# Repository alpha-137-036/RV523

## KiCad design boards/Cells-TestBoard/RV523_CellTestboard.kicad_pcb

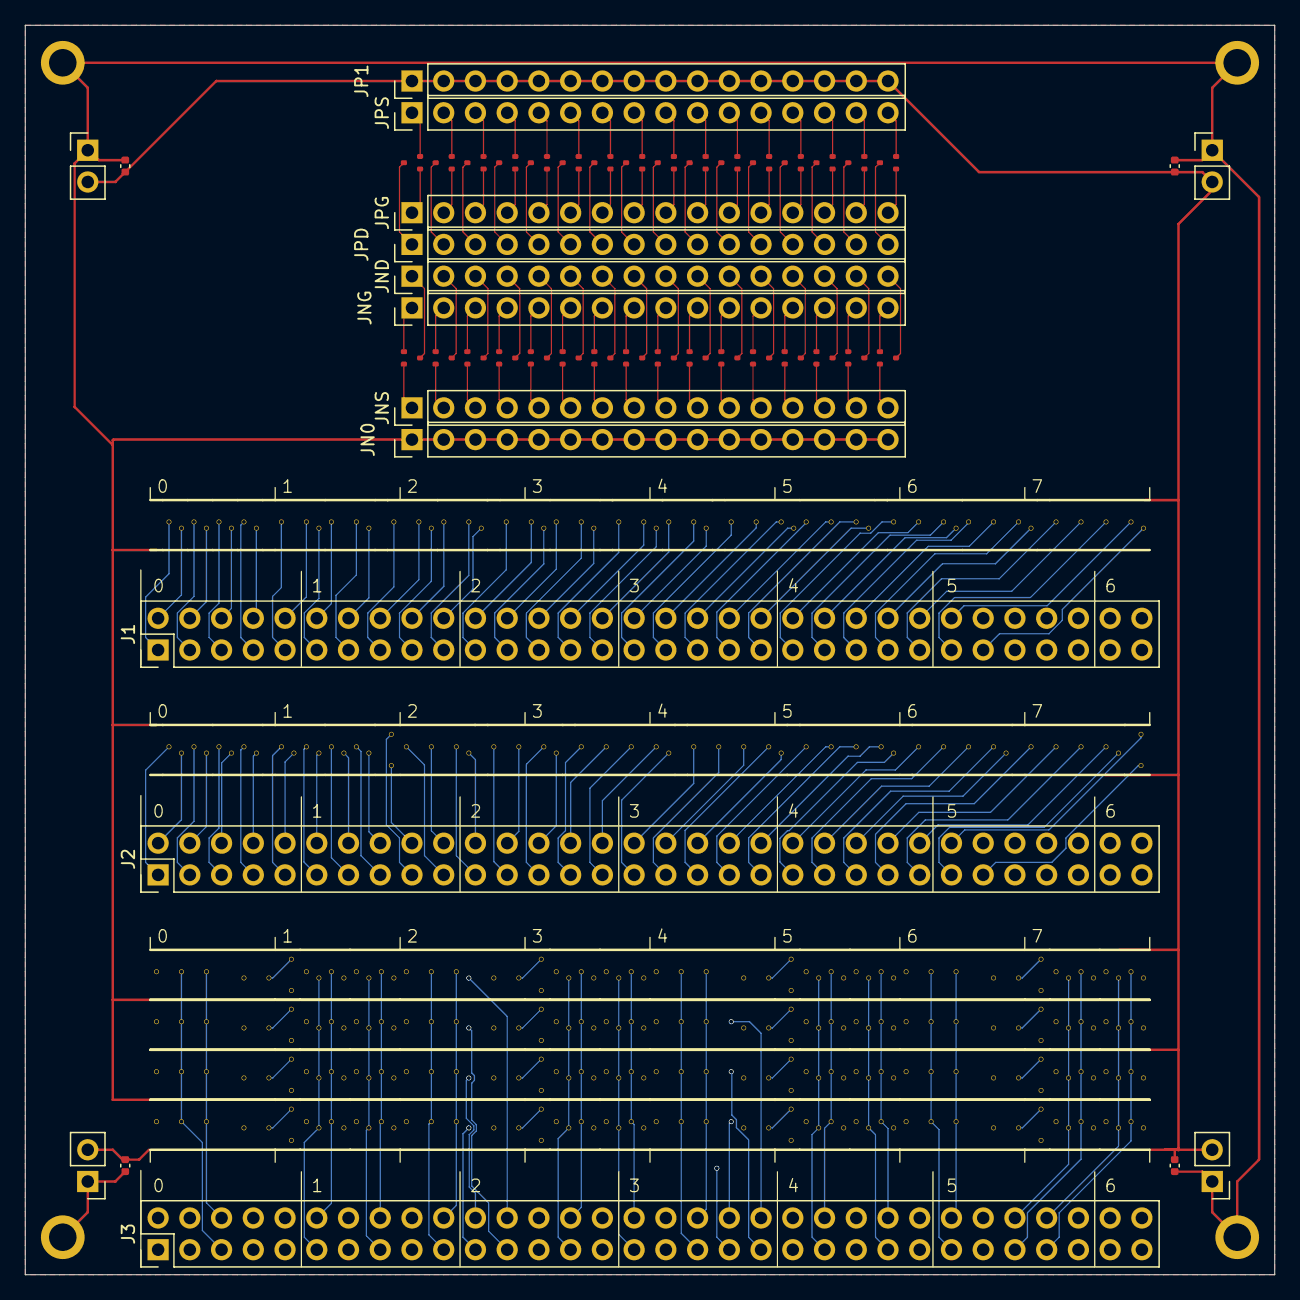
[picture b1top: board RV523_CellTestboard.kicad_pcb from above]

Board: 4 copper layers, 100.0 x 100.0 mm, 161 parts (0 on the bottom side), 276 nets.

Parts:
AOI21_1: AOI21
AOI22_1: AOI22
AOI211_1: AOI211
DECAP1, DECAP2, DECAP3, DECAP4: C_0402_1005Metric
DECAP_1, DECAP_2, DECAP_3, DECAP_4, DECAP_5, DECAP_6, DECAP_7, DECAP_8, DECAP_10, DECAP_11, DECAP_13, DECAP_14, DECAP_15, DECAP_16, DECAP_17, DECAP_18: DECAP
DECAP_LED_12, DECAP_LED_19: DECAP_LED
J1, J2, J3: PinHeader_2x32_P2.54mm_Vertical
JN0: PinHeader_1x16_P2.54mm_Vertical
JND: PinHeader_1x16_P2.54mm_Vertical
JNG: PinHeader_1x16_P2.54mm_Vertical
JNS: PinHeader_1x16_P2.54mm_Vertical
JP1: PinHeader_1x16_P2.54mm_Vertical
JPD: PinHeader_1x16_P2.54mm_Vertical
JPG: PinHeader_1x16_P2.54mm_Vertical
JPS: PinHeader_1x16_P2.54mm_Vertical
JSupply1, JSupply2, JSupply3, JSupply4: PinHeader_1x02_P2.54mm_Vertical
NAND2_1, NAND2_2, NAND2_3, NAND2_4: NAND2
NAND3_1, NAND3_2: NAND3
NAND4_1: NAND4
NOR2_1, NOR2_2, NOR2_3, NOR2_4: NOR2
NOR3_1, NOR3_2: NOR3
NOR4_1: NOR4
NOT_1, NOT_2, NOT_3, NOT_4: NOT
OAI21_1: OAI21
OAI22_1: OAI22
OAI211_1: OAI211
TINV_1, TINV_2, TINV_3, TINV_4: TINV
genblk1[1].N, genblk1[2].N, genblk1[3].N, genblk1[4].N, genblk1[5].N, genblk1[6].N, genblk1[7].N, genblk1[8].N, genblk1[9].N, genblk1[10].N, genblk1[11].N, genblk1[12].N, genblk1[13].N, genblk1[14].N, genblk1[15].N, genblk1[16].N: NMOS; SOT523
genblk1[1].P, genblk1[2].P, genblk1[3].P, genblk1[4].P, genblk1[5].P, genblk1[6].P, genblk1[7].P, genblk1[8].P, genblk1[9].P, genblk1[10].P, genblk1[11].P, genblk1[12].P, genblk1[13].P, genblk1[14].P, genblk1[15].P, genblk1[16].P: PMOS; SOT523
genblk2[0].genblk1[0].D, genblk2[0].genblk1[1].D, genblk2[0].genblk1[2].D, genblk2[0].genblk1[3].D, genblk2[1].genblk1[0].D, genblk2[1].genblk1[1].D, genblk2[1].genblk1[2].D, genblk2[1].genblk1[3].D, genblk2[2].genblk1[0].D, genblk2[2].genblk1[1].D, genblk2[2].genblk1[2].D, genblk2[2].genblk1[3].D, genblk2[3].genblk1[0].D, genblk2[3].genblk1[1].D, genblk2[3].genblk1[2].D, genblk2[3].genblk1[3].D: DECAP_LED
genblk2[0].genblk1[0].L, genblk2[0].genblk1[1].L, genblk2[0].genblk1[2].L, genblk2[0].genblk1[3].L, genblk2[1].genblk1[0].L, genblk2[1].genblk1[1].L, genblk2[1].genblk1[2].L, genblk2[1].genblk1[3].L, genblk2[2].genblk1[0].L, genblk2[2].genblk1[1].L, genblk2[2].genblk1[2].L, genblk2[2].genblk1[3].L, genblk2[3].genblk1[0].L, genblk2[3].genblk1[1].L, genblk2[3].genblk1[2].L, genblk2[3].genblk1[3].L: D_LATCH
genblk2[0].genblk1[0].R1, genblk2[0].genblk1[0].R2, genblk2[0].genblk1[1].R1, genblk2[0].genblk1[1].R2, genblk2[0].genblk1[2].R1, genblk2[0].genblk1[2].R2, genblk2[0].genblk1[3].R1, genblk2[0].genblk1[3].R2, genblk2[1].genblk1[0].R1, genblk2[1].genblk1[0].R2, genblk2[1].genblk1[1].R1, genblk2[1].genblk1[1].R2, genblk2[1].genblk1[2].R1, genblk2[1].genblk1[2].R2, genblk2[1].genblk1[3].R1, genblk2[1].genblk1[3].R2, genblk2[2].genblk1[0].R1, genblk2[2].genblk1[0].R2, genblk2[2].genblk1[1].R1, genblk2[2].genblk1[1].R2, genblk2[2].genblk1[2].R1, genblk2[2].genblk1[2].R2, genblk2[2].genblk1[3].R1, genblk2[2].genblk1[3].R2, genblk2[3].genblk1[0].R1, genblk2[3].genblk1[0].R2, genblk2[3].genblk1[1].R1, genblk2[3].genblk1[1].R2, genblk2[3].genblk1[2].R1, genblk2[3].genblk1[2].R2, genblk2[3].genblk1[3].R1, genblk2[3].genblk1[3].R2: TINV

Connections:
GND: DECAP1.2, DECAP2.2, DECAP3.2, DECAP4.2, JN0.1 (pins.1), JN0.2 (pins.2), JN0.3 (pins.3), JN0.4 (pins.4), JN0.5 (pins.5), JN0.6 (pins.6), JN0.7 (pins.7), JN0.8 (pins.8), JN0.9 (pins.9), JN0.10 (pins.10), JN0.11 (pins.11), JN0.12 (pins.12), JN0.13 (pins.13), JN0.14 (pins.14), JN0.15 (pins.15), JN0.16 (pins.16), JSupply1.1 (pins.1), JSupply2.1 (pins.1), JSupply3.1 (pins.1), JSupply4.1 (pins.1)
J1pins.9: J1.9 (pins.9), NAND2_1.A1
J1pins.10: J1.10 (pins.10), NAND2_1.A2
J1pins.12: J1.12 (pins.12), NAND2_2.A1
J1pins.13: J1.13 (pins.13), NAND2_2.A2
J1pins.15: J1.15 (pins.15), NAND2_3.A1
J1pins.16: J1.16 (pins.16), NAND2_3.A2
J1pins.18: J1.18 (pins.18), NAND2_4.A1
J1pins.19: J1.19 (pins.19), NAND2_4.A2
J1pins.21: J1.21 (pins.21), NOR2_1.A1
J1pins.22: J1.22 (pins.22), NOR2_1.A2
J1pins.24: J1.24 (pins.24), NOR2_2.A1
J1pins.25: J1.25 (pins.25), NOR2_2.A2
J1pins.27: J1.27 (pins.27), NOR2_3.A1
J1pins.28: J1.28 (pins.28), NOR2_3.A2
J1pins.30: J1.30 (pins.30), NOR2_4.A1
J1pins.31: J1.31 (pins.31), NOR2_4.A2
J1pins.33: J1.33 (pins.33), NAND3_1.A1
J1pins.34: J1.34 (pins.34), NAND3_1.A2
J1pins.35: J1.35 (pins.35), NAND3_1.A3
J1pins.37: J1.37 (pins.37), NAND3_2.A1
J1pins.38: J1.38 (pins.38), NAND3_2.A2
J1pins.39: J1.39 (pins.39), NAND3_2.A3
J1pins.41: J1.41 (pins.41), NOR3_1.A1
J1pins.42: J1.42 (pins.42), NOR3_1.A2
J1pins.43: J1.43 (pins.43), NOR3_1.A3
J1pins.45: J1.45 (pins.45), NOR3_2.A1
J1pins.46: J1.46 (pins.46), NOR3_2.A2
J1pins.47: J1.47 (pins.47), NOR3_2.A3
J1pins.49: J1.49 (pins.49), NAND4_1.A1
J1pins.50: J1.50 (pins.50), NAND4_1.A2
J1pins.51: J1.51 (pins.51), NAND4_1.A3
J1pins.52: J1.52 (pins.52), NAND4_1.A4
J1pins[1]: J1.1 (pins.1), NOT_1.A
J1pins[2]: J1.2 (pins.2), NOT_1.Y
J1pins[3]: J1.3 (pins.3), NOT_2.A
J1pins[4]: J1.4 (pins.4), NOT_2.Y
J1pins[5]: J1.5 (pins.5), NOT_3.A
J1pins[6]: J1.6 (pins.6), NOT_3.Y
J1pins[7]: J1.7 (pins.7), NOT_4.A
J1pins[8]: J1.8 (pins.8), NOT_4.Y
J1pins[11]: J1.11 (pins.11), NAND2_1.Y
J1pins[14]: J1.14 (pins.14), NAND2_2.Y
J1pins[17]: J1.17 (pins.17), NAND2_3.Y
J1pins[20]: J1.20 (pins.20), NAND2_4.Y
J1pins[23]: J1.23 (pins.23), NOR2_1.Y
J1pins[26]: J1.26 (pins.26), NOR2_2.Y
J1pins[29]: J1.29 (pins.29), NOR2_3.Y
J1pins[32]: J1.32 (pins.32), NOR2_4.Y
J1pins[36]: J1.36 (pins.36), NAND3_1.Y
J1pins[40]: J1.40 (pins.40), NAND3_2.Y
J1pins[44]: J1.44 (pins.44), NOR3_1.Y
J1pins[48]: J1.48 (pins.48), NOR3_2.Y
J1pins[53]: J1.53 (pins.53), NAND4_1.Y
J2pins.1: J2.1 (pins.1), TINV_1.A
J2pins.2: J2.2 (pins.2), TINV_1.EN
J2pins.3: J2.3 (pins.3), TINV_1.nEN
J2pins.5: J2.5 (pins.5), TINV_2.A
J2pins.6: J2.6 (pins.6), TINV_2.EN
J2pins.7: J2.7 (pins.7), TINV_2.nEN
J2pins.9: J2.9 (pins.9), TINV_3.A
J2pins.10: J2.10 (pins.10), TINV_3.EN
J2pins.11: J2.11 (pins.11), TINV_3.nEN
J2pins.13: J2.13 (pins.13), TINV_4.A
J2pins.14: J2.14 (pins.14), TINV_4.EN
J2pins.15: J2.15 (pins.15), TINV_4.nEN
J2pins.19: AOI21_1.A, J2.19 (pins.19)
J2pins.20: AOI21_1.B1, J2.20 (pins.20)
J2pins.21: AOI21_1.B2, J2.21 (pins.21)
J2pins.23: J2.23 (pins.23), OAI21_1.A
J2pins.24: J2.24 (pins.24), OAI21_1.B1
J2pins.25: J2.25 (pins.25), OAI21_1.B2
J2pins.27: AOI22_1.A1, J2.27 (pins.27)
J2pins.28: AOI22_1.A2, J2.28 (pins.28)
J2pins.29: AOI22_1.B1, J2.29 (pins.29)
J2pins.30: AOI22_1.B2, J2.30 (pins.30)
J2pins.32: J2.32 (pins.32), OAI22_1.A1
J2pins.33: J2.33 (pins.33), OAI22_1.A2
J2pins.34: J2.34 (pins.34), OAI22_1.B1
J2pins.35: J2.35 (pins.35), OAI22_1.B2
J2pins.37: AOI211_1.A, J2.37 (pins.37)
J2pins.38: AOI211_1.B, J2.38 (pins.38)
J2pins.39: AOI211_1.C1, J2.39 (pins.39)
J2pins.40: AOI211_1.C2, J2.40 (pins.40)
J2pins.42: J2.42 (pins.42), OAI211_1.A
J2pins.43: J2.43 (pins.43), OAI211_1.B
J2pins.44: J2.44 (pins.44), OAI211_1.C1
J2pins.45: J2.45 (pins.45), OAI211_1.C2
J2pins.47: J2.47 (pins.47), NOR4_1.A1
J2pins.48: J2.48 (pins.48), NOR4_1.A2
J2pins.49: J2.49 (pins.49), NOR4_1.A3
J2pins.50: J2.50 (pins.50), NOR4_1.A4
J2pins[4]: J2.4 (pins.4), TINV_1.Y
J2pins[8]: J2.8 (pins.8), TINV_2.Y
J2pins[12]: J2.12 (pins.12), TINV_3.Y
J2pins[16]: J2.16 (pins.16), TINV_4.Y
J2pins[17]: DECAP_LED_12.A, J2.17 (pins.17)
J2pins[18]: DECAP_LED_12.LED_GND, J2.18 (pins.18)
J2pins[22]: AOI21_1.Y, J2.22 (pins.22)
J2pins[26]: J2.26 (pins.26), OAI21_1.Y
J2pins[31]: AOI22_1.Y, J2.31 (pins.31)
J2pins[36]: J2.36 (pins.36), OAI22_1.Y
J2pins[41]: AOI211_1.Y, J2.41 (pins.41)
J2pins[46]: J2.46 (pins.46), OAI211_1.Y
J2pins[51]: J2.51 (pins.51), NOR4_1.Y
J2pins[52]: DECAP_LED_19.A, J2.52 (pins.52)
J2pins[53]: DECAP_LED_19.LED_GND, J2.53 (pins.53)
J3pins.1: J3.1 (pins.1), genblk2[0].genblk1[0].L.D, genblk2[1].genblk1[0].L.D, genblk2[2].genblk1[0].L.D, genblk2[3].genblk1[0].L.D
J3pins.2: J3.2 (pins.2), genblk2[0].genblk1[1].L.D, genblk2[1].genblk1[1].L.D, genblk2[2].genblk1[1].L.D, genblk2[3].genblk1[1].L.D
J3pins.3: J3.3 (pins.3), genblk2[0].genblk1[2].L.D, genblk2[1].genblk1[2].L.D, genblk2[2].genblk1[2].L.D, genblk2[3].genblk1[2].L.D
J3pins.4: J3.4 (pins.4), genblk2[0].genblk1[3].L.D, genblk2[1].genblk1[3].L.D, genblk2[2].genblk1[3].L.D, genblk2[3].genblk1[3].L.D
J3pins.5: J3.5 (pins.5), genblk2[0].genblk1[0].L.CLK, genblk2[0].genblk1[1].L.CLK, genblk2[0].genblk1[2].L.CLK, genblk2[0].genblk1[3].L.CLK
J3pins.6: J3.6 (pins.6), genblk2[0].genblk1[0].L.nCLK, genblk2[0].genblk1[1].L.nCLK, genblk2[0].genblk1[2].L.nCLK, genblk2[0].genblk1[3].L.nCLK
J3pins.11: J3.11 (pins.11), genblk2[0].genblk1[0].R1.EN, genblk2[0].genblk1[1].R1.EN, genblk2[0].genblk1[2].R1.EN, genblk2[0].genblk1[3].R1.EN
J3pins.12: J3.12 (pins.12), genblk2[0].genblk1[0].R1.nEN, genblk2[0].genblk1[1].R1.nEN, genblk2[0].genblk1[2].R1.nEN, genblk2[0].genblk1[3].R1.nEN
J3pins.15: J3.15 (pins.15), genblk2[0].genblk1[0].R2.EN, genblk2[0].genblk1[1].R2.EN, genblk2[0].genblk1[2].R2.EN, genblk2[0].genblk1[3].R2.EN
J3pins.16: J3.16 (pins.16), genblk2[0].genblk1[0].R2.nEN, genblk2[0].genblk1[1].R2.nEN, genblk2[0].genblk1[2].R2.nEN, genblk2[0].genblk1[3].R2.nEN
J3pins.19: J3.19 (pins.19), genblk2[1].genblk1[0].L.CLK, genblk2[1].genblk1[1].L.CLK, genblk2[1].genblk1[2].L.CLK, genblk2[1].genblk1[3].L.CLK
J3pins.20: J3.20 (pins.20), genblk2[1].genblk1[0].L.nCLK, genblk2[1].genblk1[1].L.nCLK, genblk2[1].genblk1[2].L.nCLK, genblk2[1].genblk1[3].L.nCLK
J3pins.27: J3.27 (pins.27), genblk2[1].genblk1[0].R1.EN, genblk2[1].genblk1[1].R1.EN, genblk2[1].genblk1[2].R1.EN, genblk2[1].genblk1[3].R1.EN
J3pins.28: J3.28 (pins.28), genblk2[1].genblk1[0].R1.nEN, genblk2[1].genblk1[1].R1.nEN, genblk2[1].genblk1[2].R1.nEN, genblk2[1].genblk1[3].R1.nEN
J3pins.31: J3.31 (pins.31), genblk2[1].genblk1[0].R2.EN, genblk2[1].genblk1[1].R2.EN, genblk2[1].genblk1[2].R2.EN, genblk2[1].genblk1[3].R2.EN
J3pins.32: J3.32 (pins.32), genblk2[1].genblk1[0].R2.nEN, genblk2[1].genblk1[1].R2.nEN, genblk2[1].genblk1[2].R2.nEN, genblk2[1].genblk1[3].R2.nEN
J3pins.35: J3.35 (pins.35), genblk2[2].genblk1[0].L.CLK, genblk2[2].genblk1[1].L.CLK, genblk2[2].genblk1[2].L.CLK, genblk2[2].genblk1[3].L.CLK
J3pins.36: J3.36 (pins.36), genblk2[2].genblk1[0].L.nCLK, genblk2[2].genblk1[1].L.nCLK, genblk2[2].genblk1[2].L.nCLK, genblk2[2].genblk1[3].L.nCLK
J3pins.43: J3.43 (pins.43), genblk2[2].genblk1[0].R1.EN, genblk2[2].genblk1[1].R1.EN, genblk2[2].genblk1[2].R1.EN, genblk2[2].genblk1[3].R1.EN
J3pins.44: J3.44 (pins.44), genblk2[2].genblk1[0].R1.nEN, genblk2[2].genblk1[1].R1.nEN, genblk2[2].genblk1[2].R1.nEN, genblk2[2].genblk1[3].R1.nEN
J3pins.47: J3.47 (pins.47), genblk2[2].genblk1[0].R2.EN, genblk2[2].genblk1[1].R2.EN, genblk2[2].genblk1[2].R2.EN, genblk2[2].genblk1[3].R2.EN
J3pins.48: J3.48 (pins.48), genblk2[2].genblk1[0].R2.nEN, genblk2[2].genblk1[1].R2.nEN, genblk2[2].genblk1[2].R2.nEN, genblk2[2].genblk1[3].R2.nEN
J3pins.51: J3.51 (pins.51), genblk2[3].genblk1[0].L.CLK, genblk2[3].genblk1[1].L.CLK, genblk2[3].genblk1[2].L.CLK, genblk2[3].genblk1[3].L.CLK
J3pins.52: J3.52 (pins.52), genblk2[3].genblk1[0].L.nCLK, genblk2[3].genblk1[1].L.nCLK, genblk2[3].genblk1[2].L.nCLK, genblk2[3].genblk1[3].L.nCLK
J3pins.55: J3.55 (pins.55), genblk2[3].genblk1[0].R1.nEN, genblk2[3].genblk1[1].R1.nEN, genblk2[3].genblk1[2].R1.nEN, genblk2[3].genblk1[3].R1.nEN
J3pins.56: J3.56 (pins.56), genblk2[3].genblk1[0].R1.EN, genblk2[3].genblk1[1].R1.EN, genblk2[3].genblk1[2].R1.EN, genblk2[3].genblk1[3].R1.EN
J3pins.57: J3.57 (pins.57), genblk2[3].genblk1[0].R2.nEN, genblk2[3].genblk1[1].R2.nEN, genblk2[3].genblk1[2].R2.nEN, genblk2[3].genblk1[3].R2.nEN
J3pins.58: J3.58 (pins.58), genblk2[3].genblk1[0].R2.EN, genblk2[3].genblk1[1].R2.EN, genblk2[3].genblk1[2].R2.EN, genblk2[3].genblk1[3].R2.EN
J3pins[21]: J3.21 (pins.21), genblk2[0].genblk1[3].R1.Y, genblk2[1].genblk1[3].R1.Y, genblk2[2].genblk1[3].R1.Y, genblk2[3].genblk1[3].R1.Y
J3pins[22]: J3.22 (pins.22), genblk2[0].genblk1[2].R1.Y, genblk2[1].genblk1[2].R1.Y, genblk2[2].genblk1[2].R1.Y, genblk2[3].genblk1[2].R1.Y
J3pins[23]: J3.23 (pins.23), genblk2[0].genblk1[1].R1.Y, genblk2[1].genblk1[1].R1.Y, genblk2[2].genblk1[1].R1.Y, genblk2[3].genblk1[1].R1.Y
J3pins[24]: J3.24 (pins.24), genblk2[0].genblk1[0].R1.Y, genblk2[1].genblk1[0].R1.Y, genblk2[2].genblk1[0].R1.Y, genblk2[3].genblk1[0].R1.Y
J3pins[37]: J3.37 (pins.37), genblk2[0].genblk1[3].R2.Y, genblk2[1].genblk1[3].R2.Y, genblk2[2].genblk1[3].R2.Y, genblk2[3].genblk1[3].R2.Y
J3pins[38]: J3.38 (pins.38), genblk2[0].genblk1[2].R2.Y, genblk2[1].genblk1[2].R2.Y, genblk2[2].genblk1[2].R2.Y, genblk2[3].genblk1[2].R2.Y
J3pins[39]: J3.39 (pins.39), genblk2[0].genblk1[1].R2.Y, genblk2[1].genblk1[1].R2.Y, genblk2[2].genblk1[1].R2.Y, genblk2[3].genblk1[1].R2.Y
J3pins[40]: J3.40 (pins.40), genblk2[0].genblk1[0].R2.Y, genblk2[1].genblk1[0].R2.Y, genblk2[2].genblk1[0].R2.Y, genblk2[3].genblk1[0].R2.Y
J3pins[61]: J3.61 (pins.61), genblk2[0].genblk1[3].D.LED_GND, genblk2[1].genblk1[3].D.LED_GND, genblk2[2].genblk1[3].D.LED_GND, genblk2[3].genblk1[3].D.LED_GND
J3pins[62]: J3.62 (pins.62), genblk2[0].genblk1[2].D.LED_GND, genblk2[1].genblk1[2].D.LED_GND, genblk2[2].genblk1[2].D.LED_GND, genblk2[3].genblk1[2].D.LED_GND
J3pins[63]: J3.63 (pins.63), genblk2[0].genblk1[1].D.LED_GND, genblk2[1].genblk1[1].D.LED_GND, genblk2[2].genblk1[1].D.LED_GND, genblk2[3].genblk1[1].D.LED_GND
J3pins[64]: J3.64 (pins.64), genblk2[0].genblk1[0].D.LED_GND, genblk2[1].genblk1[0].D.LED_GND, genblk2[2].genblk1[0].D.LED_GND, genblk2[3].genblk1[0].D.LED_GND
NDrains[1]: JND.1 (pins.1), genblk1[1].N.3 (D)
NDrains[2]: JND.2 (pins.2), genblk1[2].N.3 (D)
NDrains[3]: JND.3 (pins.3), genblk1[3].N.3 (D)
NDrains[4]: JND.4 (pins.4), genblk1[4].N.3 (D)
NDrains[5]: JND.5 (pins.5), genblk1[5].N.3 (D)
NDrains[6]: JND.6 (pins.6), genblk1[6].N.3 (D)
NDrains[7]: JND.7 (pins.7), genblk1[7].N.3 (D)
NDrains[8]: JND.8 (pins.8), genblk1[8].N.3 (D)
NDrains[9]: JND.9 (pins.9), genblk1[9].N.3 (D)
NDrains[10]: JND.10 (pins.10), genblk1[10].N.3 (D)
NDrains[11]: JND.11 (pins.11), genblk1[11].N.3 (D)
NDrains[12]: JND.12 (pins.12), genblk1[12].N.3 (D)
NDrains[13]: JND.13 (pins.13), genblk1[13].N.3 (D)
NDrains[14]: JND.14 (pins.14), genblk1[14].N.3 (D)
NDrains[15]: JND.15 (pins.15), genblk1[15].N.3 (D)
NDrains[16]: JND.16 (pins.16), genblk1[16].N.3 (D)
NGates[1]: JNG.1 (pins.1), genblk1[1].N.1 (G)
NGates[2]: JNG.2 (pins.2), genblk1[2].N.1 (G)
NGates[3]: JNG.3 (pins.3), genblk1[3].N.1 (G)
NGates[4]: JNG.4 (pins.4), genblk1[4].N.1 (G)
NGates[5]: JNG.5 (pins.5), genblk1[5].N.1 (G)
NGates[6]: JNG.6 (pins.6), genblk1[6].N.1 (G)
NGates[7]: JNG.7 (pins.7), genblk1[7].N.1 (G)
NGates[8]: JNG.8 (pins.8), genblk1[8].N.1 (G)
NGates[9]: JNG.9 (pins.9), genblk1[9].N.1 (G)
NGates[10]: JNG.10 (pins.10), genblk1[10].N.1 (G)
NGates[11]: JNG.11 (pins.11), genblk1[11].N.1 (G)
NGates[12]: JNG.12 (pins.12), genblk1[12].N.1 (G)
NGates[13]: JNG.13 (pins.13), genblk1[13].N.1 (G)
NGates[14]: JNG.14 (pins.14), genblk1[14].N.1 (G)
NGates[15]: JNG.15 (pins.15), genblk1[15].N.1 (G)
NGates[16]: JNG.16 (pins.16), genblk1[16].N.1 (G)
NSources[1]: JNS.1 (pins.1), genblk1[1].N.2 (S)
NSources[2]: JNS.2 (pins.2), genblk1[2].N.2 (S)
NSources[3]: JNS.3 (pins.3), genblk1[3].N.2 (S)
NSources[4]: JNS.4 (pins.4), genblk1[4].N.2 (S)
NSources[5]: JNS.5 (pins.5), genblk1[5].N.2 (S)
NSources[6]: JNS.6 (pins.6), genblk1[6].N.2 (S)
NSources[7]: JNS.7 (pins.7), genblk1[7].N.2 (S)
NSources[8]: JNS.8 (pins.8), genblk1[8].N.2 (S)
NSources[9]: JNS.9 (pins.9), genblk1[9].N.2 (S)
NSources[10]: JNS.10 (pins.10), genblk1[10].N.2 (S)
NSources[11]: JNS.11 (pins.11), genblk1[11].N.2 (S)
NSources[12]: JNS.12 (pins.12), genblk1[12].N.2 (S)
NSources[13]: JNS.13 (pins.13), genblk1[13].N.2 (S)
NSources[14]: JNS.14 (pins.14), genblk1[14].N.2 (S)
NSources[15]: JNS.15 (pins.15), genblk1[15].N.2 (S)
NSources[16]: JNS.16 (pins.16), genblk1[16].N.2 (S)
PDrains[1]: JPD.1 (pins.1), genblk1[1].P.3 (D)
PDrains[2]: JPD.2 (pins.2), genblk1[2].P.3 (D)
PDrains[3]: JPD.3 (pins.3), genblk1[3].P.3 (D)
PDrains[4]: JPD.4 (pins.4), genblk1[4].P.3 (D)
PDrains[5]: JPD.5 (pins.5), genblk1[5].P.3 (D)
PDrains[6]: JPD.6 (pins.6), genblk1[6].P.3 (D)
PDrains[7]: JPD.7 (pins.7), genblk1[7].P.3 (D)
PDrains[8]: JPD.8 (pins.8), genblk1[8].P.3 (D)
PDrains[9]: JPD.9 (pins.9), genblk1[9].P.3 (D)
PDrains[10]: JPD.10 (pins.10), genblk1[10].P.3 (D)
PDrains[11]: JPD.11 (pins.11), genblk1[11].P.3 (D)
PDrains[12]: JPD.12 (pins.12), genblk1[12].P.3 (D)
PDrains[13]: JPD.13 (pins.13), genblk1[13].P.3 (D)
PDrains[14]: JPD.14 (pins.14), genblk1[14].P.3 (D)
PDrains[15]: JPD.15 (pins.15), genblk1[15].P.3 (D)
PDrains[16]: JPD.16 (pins.16), genblk1[16].P.3 (D)
PGates[1]: JPG.1 (pins.1), genblk1[1].P.1 (G)
PGates[2]: JPG.2 (pins.2), genblk1[2].P.1 (G)
PGates[3]: JPG.3 (pins.3), genblk1[3].P.1 (G)
PGates[4]: JPG.4 (pins.4), genblk1[4].P.1 (G)
PGates[5]: JPG.5 (pins.5), genblk1[5].P.1 (G)
PGates[6]: JPG.6 (pins.6), genblk1[6].P.1 (G)
PGates[7]: JPG.7 (pins.7), genblk1[7].P.1 (G)
PGates[8]: JPG.8 (pins.8), genblk1[8].P.1 (G)
PGates[9]: JPG.9 (pins.9), genblk1[9].P.1 (G)
PGates[10]: JPG.10 (pins.10), genblk1[10].P.1 (G)
PGates[11]: JPG.11 (pins.11), genblk1[11].P.1 (G)
PGates[12]: JPG.12 (pins.12), genblk1[12].P.1 (G)
PGates[13]: JPG.13 (pins.13), genblk1[13].P.1 (G)
PGates[14]: JPG.14 (pins.14), genblk1[14].P.1 (G)
PGates[15]: JPG.15 (pins.15), genblk1[15].P.1 (G)
PGates[16]: JPG.16 (pins.16), genblk1[16].P.1 (G)
PSources[1]: JPS.1 (pins.1), genblk1[1].P.2 (S)
PSources[2]: JPS.2 (pins.2), genblk1[2].P.2 (S)
PSources[3]: JPS.3 (pins.3), genblk1[3].P.2 (S)
PSources[4]: JPS.4 (pins.4), genblk1[4].P.2 (S)
PSources[5]: JPS.5 (pins.5), genblk1[5].P.2 (S)
PSources[6]: JPS.6 (pins.6), genblk1[6].P.2 (S)
PSources[7]: JPS.7 (pins.7), genblk1[7].P.2 (S)
PSources[8]: JPS.8 (pins.8), genblk1[8].P.2 (S)
PSources[9]: JPS.9 (pins.9), genblk1[9].P.2 (S)
PSources[10]: JPS.10 (pins.10), genblk1[10].P.2 (S)
PSources[11]: JPS.11 (pins.11), genblk1[11].P.2 (S)
PSources[12]: JPS.12 (pins.12), genblk1[12].P.2 (S)
PSources[13]: JPS.13 (pins.13), genblk1[13].P.2 (S)
PSources[14]: JPS.14 (pins.14), genblk1[14].P.2 (S)
PSources[15]: JPS.15 (pins.15), genblk1[15].P.2 (S)
PSources[16]: JPS.16 (pins.16), genblk1[16].P.2 (S)
VDD: DECAP1.1, DECAP2.1, DECAP3.1, DECAP4.1, JP1.1 (pins.1), JP1.2 (pins.2), JP1.3 (pins.3), JP1.4 (pins.4), JP1.5 (pins.5), JP1.6 (pins.6), JP1.7 (pins.7), JP1.8 (pins.8), JP1.9 (pins.9), JP1.10 (pins.10), JP1.11 (pins.11), JP1.12 (pins.12), JP1.13 (pins.13), JP1.14 (pins.14), JP1.15 (pins.15), JP1.16 (pins.16), JSupply1.2 (pins.2), JSupply2.2 (pins.2), JSupply3.2 (pins.2), JSupply4.2 (pins.2)
genblk2[0].genblk1[0].Q: genblk2[0].genblk1[0].D.A, genblk2[0].genblk1[0].L.Q
genblk2[0].genblk1[0].nQ: genblk2[0].genblk1[0].L.nQ, genblk2[0].genblk1[0].R1.A, genblk2[0].genblk1[0].R2.A
genblk2[0].genblk1[1].Q: genblk2[0].genblk1[1].D.A, genblk2[0].genblk1[1].L.Q
genblk2[0].genblk1[1].nQ: genblk2[0].genblk1[1].L.nQ, genblk2[0].genblk1[1].R1.A, genblk2[0].genblk1[1].R2.A
genblk2[0].genblk1[2].Q: genblk2[0].genblk1[2].D.A, genblk2[0].genblk1[2].L.Q
genblk2[0].genblk1[2].nQ: genblk2[0].genblk1[2].L.nQ, genblk2[0].genblk1[2].R1.A, genblk2[0].genblk1[2].R2.A
genblk2[0].genblk1[3].Q: genblk2[0].genblk1[3].D.A, genblk2[0].genblk1[3].L.Q
genblk2[0].genblk1[3].nQ: genblk2[0].genblk1[3].L.nQ, genblk2[0].genblk1[3].R1.A, genblk2[0].genblk1[3].R2.A
genblk2[1].genblk1[0].Q: genblk2[1].genblk1[0].D.A, genblk2[1].genblk1[0].L.Q
genblk2[1].genblk1[0].nQ: genblk2[1].genblk1[0].L.nQ, genblk2[1].genblk1[0].R1.A, genblk2[1].genblk1[0].R2.A
genblk2[1].genblk1[1].Q: genblk2[1].genblk1[1].D.A, genblk2[1].genblk1[1].L.Q
genblk2[1].genblk1[1].nQ: genblk2[1].genblk1[1].L.nQ, genblk2[1].genblk1[1].R1.A, genblk2[1].genblk1[1].R2.A
genblk2[1].genblk1[2].Q: genblk2[1].genblk1[2].D.A, genblk2[1].genblk1[2].L.Q
genblk2[1].genblk1[2].nQ: genblk2[1].genblk1[2].L.nQ, genblk2[1].genblk1[2].R1.A, genblk2[1].genblk1[2].R2.A
genblk2[1].genblk1[3].Q: genblk2[1].genblk1[3].D.A, genblk2[1].genblk1[3].L.Q
genblk2[1].genblk1[3].nQ: genblk2[1].genblk1[3].L.nQ, genblk2[1].genblk1[3].R1.A, genblk2[1].genblk1[3].R2.A
genblk2[2].genblk1[0].Q: genblk2[2].genblk1[0].D.A, genblk2[2].genblk1[0].L.Q
genblk2[2].genblk1[0].nQ: genblk2[2].genblk1[0].L.nQ, genblk2[2].genblk1[0].R1.A, genblk2[2].genblk1[0].R2.A
genblk2[2].genblk1[1].Q: genblk2[2].genblk1[1].D.A, genblk2[2].genblk1[1].L.Q
genblk2[2].genblk1[1].nQ: genblk2[2].genblk1[1].L.nQ, genblk2[2].genblk1[1].R1.A, genblk2[2].genblk1[1].R2.A
genblk2[2].genblk1[2].Q: genblk2[2].genblk1[2].D.A, genblk2[2].genblk1[2].L.Q
genblk2[2].genblk1[2].nQ: genblk2[2].genblk1[2].L.nQ, genblk2[2].genblk1[2].R1.A, genblk2[2].genblk1[2].R2.A
genblk2[2].genblk1[3].Q: genblk2[2].genblk1[3].D.A, genblk2[2].genblk1[3].L.Q
genblk2[2].genblk1[3].nQ: genblk2[2].genblk1[3].L.nQ, genblk2[2].genblk1[3].R1.A, genblk2[2].genblk1[3].R2.A
genblk2[3].genblk1[0].Q: genblk2[3].genblk1[0].D.A, genblk2[3].genblk1[0].L.Q
genblk2[3].genblk1[0].nQ: genblk2[3].genblk1[0].L.nQ, genblk2[3].genblk1[0].R1.A, genblk2[3].genblk1[0].R2.A
genblk2[3].genblk1[1].Q: genblk2[3].genblk1[1].D.A, genblk2[3].genblk1[1].L.Q
genblk2[3].genblk1[1].nQ: genblk2[3].genblk1[1].L.nQ, genblk2[3].genblk1[1].R1.A, genblk2[3].genblk1[1].R2.A
genblk2[3].genblk1[2].Q: genblk2[3].genblk1[2].D.A, genblk2[3].genblk1[2].L.Q
genblk2[3].genblk1[2].nQ: genblk2[3].genblk1[2].L.nQ, genblk2[3].genblk1[2].R1.A, genblk2[3].genblk1[2].R2.A
genblk2[3].genblk1[3].Q: genblk2[3].genblk1[3].D.A, genblk2[3].genblk1[3].L.Q
genblk2[3].genblk1[3].nQ: genblk2[3].genblk1[3].L.nQ, genblk2[3].genblk1[3].R1.A, genblk2[3].genblk1[3].R2.A
